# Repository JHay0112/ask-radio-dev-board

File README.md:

# ASK Radio Development Board

Development board for the MICRF113 - an amplitude shift keying (ASK) radio transmitter IC.

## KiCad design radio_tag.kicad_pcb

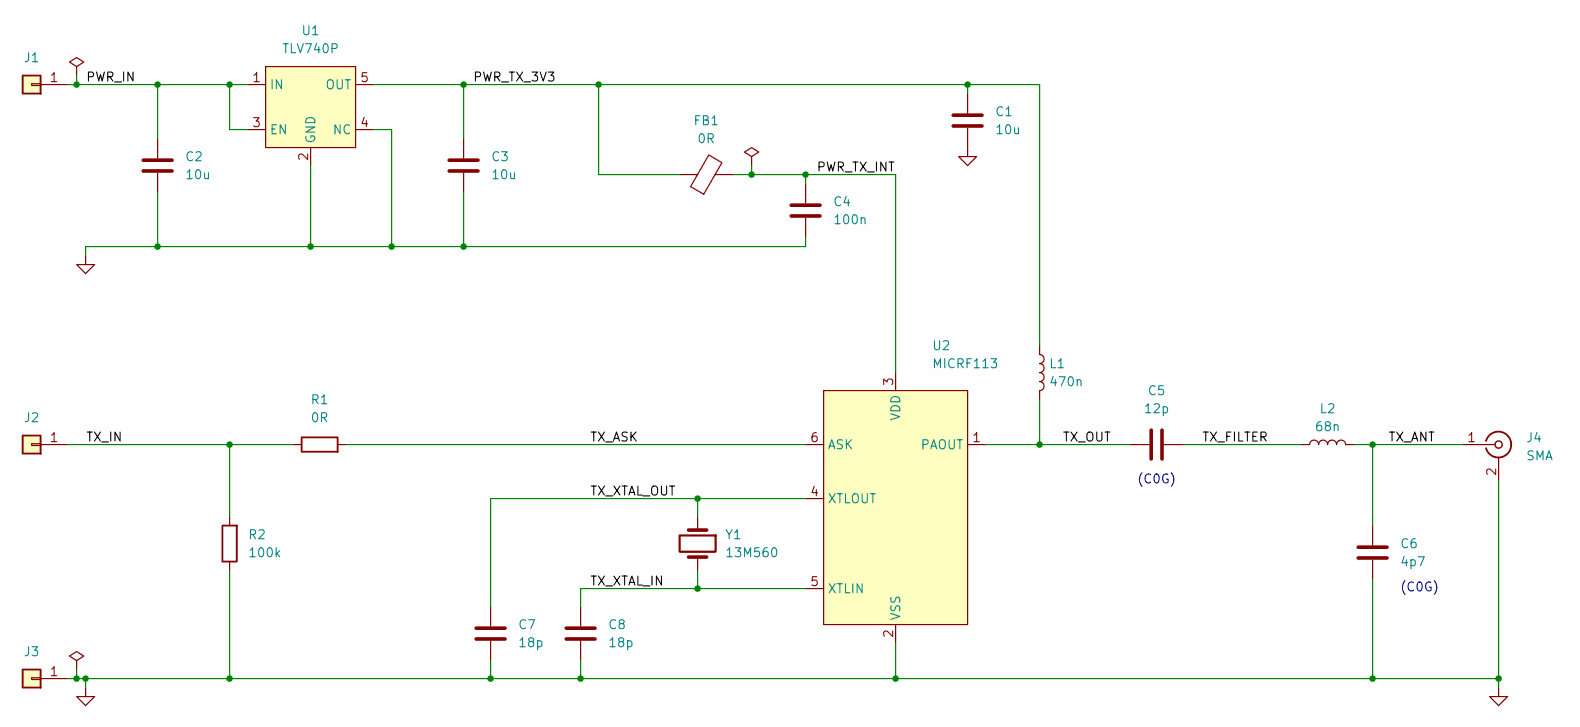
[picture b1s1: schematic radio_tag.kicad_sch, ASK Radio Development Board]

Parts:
C1, C2, C3: 10u; C_0805_2012Metric; Manufacturer PN CL21A106KOQNNNG
C4: 100n; C_0805_2012Metric; Manufacturer PN CC0805KRX7R9BB104
C5: 12p; C_0805_2012Metric; Manufacturer PN CHV0805N250120FCT
C6: 4p7; C_0805_2012Metric; Manufacturer PN CHV0805N2504R7CCT
C7, C8: 18p; C_0805_2012Metric; Manufacturer PN CC0805JRNPO9BN180
FB1: 0R; R_0805_2012Metric; Manufacturer PN RMCF0805ZT0R00
J1, J2, J3: Conn_01x01; PinHeader_1x01_P2.54mm_Vertical
J4: SMA; SMA_Samtec_SMA-J-P-H-ST-EM1_EdgeMount; Manufacturer PN CON-SMA-EDGE-S
L1: 470n; L_0805_2012Metric; Manufacturer PN LQW18ANR47J00D
L2: 68n; L_0805_2012Metric; Manufacturer PN LRC0603CJ68NGV001T
R1: 0R; R_0805_2012Metric; Manufacturer PN RMCF0805ZT0R00
R2: 100k; R_0805_2012Metric; Manufacturer PN RMCF0805JT100K
U1: TLV740P; SOT-23-5; Manufacturer PN TLV74033PDBVR
U2: MICRF113; SOT-23-6; Manufacturer PN MICRF113YM6-TR
Y1: 13M560; Crystal_SMD_HC49-SD; Manufacturer PN ABLS-13.560MHZ-10-R20-D-T

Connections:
/PWR_IN: C2.1, J1.1, U1.1 (IN), U1.3 (EN)
/PWR_TX_3V3: C1.1, C3.1, FB1.1, L1.1, U1.5 (OUT)
/PWR_TX_INT: C4.1, FB1.2, U2.3 (VDD)
/TX_ANT: C6.1, J4.1 (In), L2.2
/TX_ASK: R1.2, U2.6 (ASK)
/TX_FILTER: C5.2, L2.1
/TX_IN: J2.1, R1.1, R2.2
/TX_OUT: C5.1, L1.2, U2.1 (PAOUT)
/TX_XTAL_IN: C8.2, U2.5 (XTLIN), Y1.2
/TX_XTAL_OUT: C7.2, U2.4 (XTLOUT), Y1.1
GND: C1.2, C2.2, C3.2, C4.2, C6.2, C7.1, C8.1, J3.1, J4.2 (Ext), R2.1, U1.2 (GND), U1.4 (NC), U2.2 (VSS)

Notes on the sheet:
(C0G)

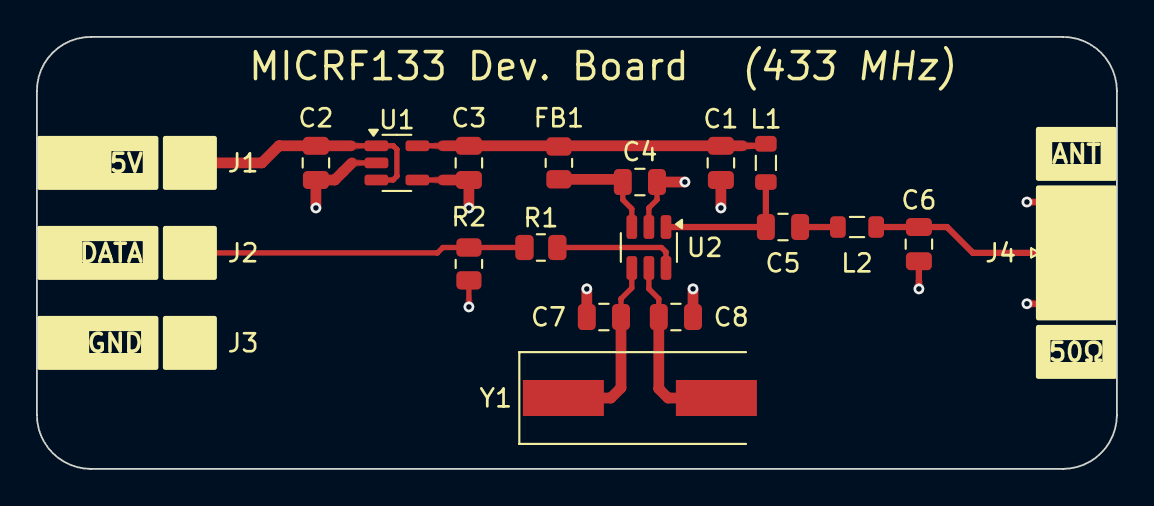
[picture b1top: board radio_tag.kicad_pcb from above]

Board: 4 copper layers, 60.0 x 24.0 mm, 20 parts (0 on the bottom side), 11 nets.

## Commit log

2025-01-31 Initial commit, setup .gitignore, README, and KiCAD project
2025-01-31 Set out schematic for MICRF113
2025-02-01 Add regulator and complete PN selection
2025-02-01 Rough out component positions, remove incorrect antenna
2025-02-01 Switch component values for 433 MHz operation
2025-02-01 Select new antenna and add to layout
2025-02-01 Route PCB
2025-02-02 Revise board to use SMA edge mount connector, mark as Rev. B
2025-02-02 Add notes for dimensions and stackup
